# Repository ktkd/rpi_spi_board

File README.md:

# Orange pi spi board
KiCAD project with SPI NOR flash module (W25QXX DataFlash Board) for orange pi/raspberry pi

This board allow you to boot Orange PI directly from SPI Nor flash without SD card.

  for reference (http://linux-sunxi.org/Bootable_SPI_flash)

sunxi-fel output from orange pi pc and this board with 25q16 spi chip:
```
$ ./sunxi-fel spiflash-info
Manufacturer: Unknown (C8h), model: 40h, size: 2097152 bytes.
```

Components:
```
SPI flash SOIC-8 25 series (for examble 25q08 and above)
PLD-6 (DS1021-2x3S) 2.54mm (for jumper selector)
PBD-8 (DS1023 2x4) 2.54mm (for orange pi connector)
0805 resistor 10Ohm (for led)
0805 led 
```

connect board to red pins (pins 17-24 onboard SPI0)

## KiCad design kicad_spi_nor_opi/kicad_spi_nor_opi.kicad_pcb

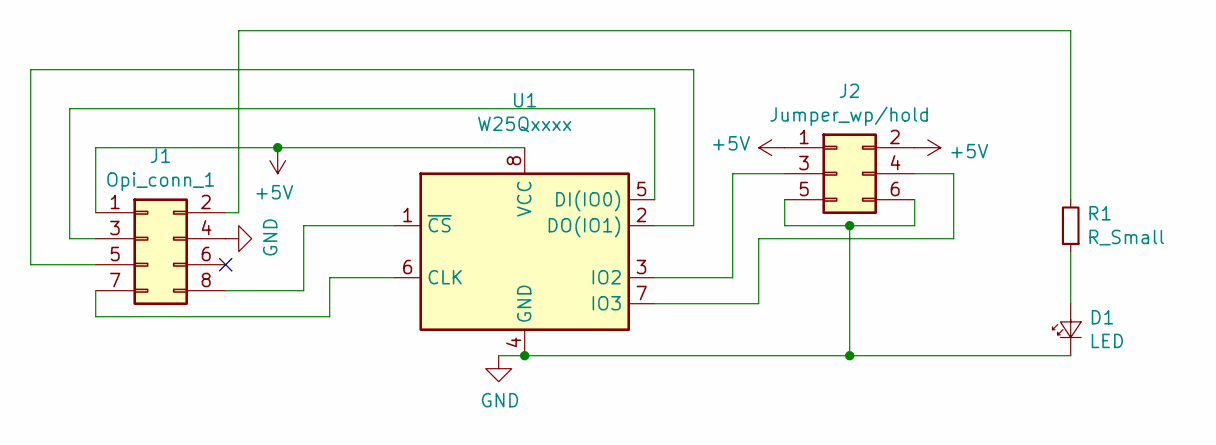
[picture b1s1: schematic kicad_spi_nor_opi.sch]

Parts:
D1: LED; LED_0805_2012Metric
J1: Opi_conn_1; PinHeader_2x04_P2.54mm_Vertical
J2: Jumper_wp/hold; PinSocket_2x03_P2.54mm_Vertical
R1: R_Small; R_0805_2012Metric
U1: W25Qxxxx; SOIC-8_5.23x5.23mm_P1.27mm

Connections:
+5V: J1.1, J2.1, J2.2, U1.8 (VCC)
GND: D1.1 (K), J1.4, J2.5, J2.6, U1.4 (GND)
unnamed: D1.2 (A), R1.1
unnamed: J1.2, R1.2
unnamed: J1.3, U1.5 (DI(IO0))
unnamed: J1.5, U1.2 (DO(IO1))
unnamed: J1.7, U1.6 (CLK)
unnamed: J1.8, U1.1 (~CS)
unnamed: J2.3, U1.3 (IO2)
unnamed: J2.4, U1.7 (IO3)

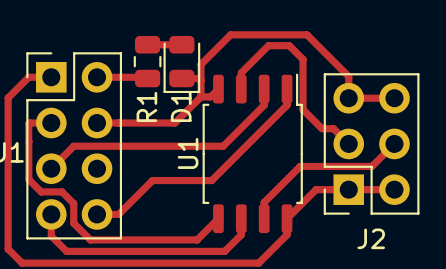
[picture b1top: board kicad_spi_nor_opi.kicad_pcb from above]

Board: 2 copper layers, 5 parts (0 on the bottom side), 10 nets.

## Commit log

2019-06-06 initial
2019-06-06 add description
2019-06-06 pre print
2019-06-06 remove files
2019-07-15 add photo
2019-07-16 final image
2019-11-10 Added gerbers to produce at jlcpcb factory
2020-05-23 Create LICENSE
